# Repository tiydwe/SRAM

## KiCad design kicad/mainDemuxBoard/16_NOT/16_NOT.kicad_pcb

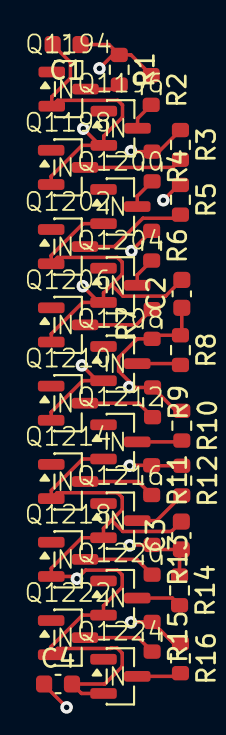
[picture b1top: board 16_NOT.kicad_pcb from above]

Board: 4 copper layers, 36 parts (0 on the bottom side), 18 nets.

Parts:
C1, C2, C3, C4: 100nC; C_0603_1608Metric
Q1194, Q1196, Q1198, Q1200, Q1202, Q1204, Q1206, Q1208, Q1210, Q1212, Q1214, Q1216, Q1218, Q1220, Q1222, Q1224: Q_NMOS_GSD; SOT-23-N
R1, R2, R3, R4, R5, R6, R7, R8, R9, R10, R11, R12, R13, R14, R15, R16: 10kR; R_0603_1608Metric

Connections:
+5V: C1.1, C2.1, C3.1, C4.1, R1.1, R2.1, R3.1, R4.1, R5.1, R6.1, R7.1, R8.1, R9.1, R10.1, R11.1, R12.1, R13.1, R14.1, R15.1, R16.1
/~Y_{0}: Q1194.3 (D), R1.2
/~Y_{1}: Q1196.3 (D), R2.2
/~Y_{2}: Q1198.3 (D), R3.2
/~Y_{3}: Q1200.3 (D), R4.2
/~Y_{4}: Q1202.3 (D), R5.2
/~Y_{5}: Q1204.3 (D), R6.2
/~Y_{6}: Q1206.3 (D), R7.2
/~Y_{7}: Q1208.3 (D), R8.2
/~Y_{8}: Q1210.3 (D), R9.2
/~Y_{9}: Q1212.3 (D), R10.2
/~Y_{10}: Q1214.3 (D), R11.2
/~Y_{11}: Q1216.3 (D), R12.2
/~Y_{12}: Q1218.3 (D), R13.2
/~Y_{13}: Q1220.3 (D), R14.2
/~Y_{14}: Q1222.3 (D), R15.2
/~Y_{15}: Q1224.3 (D), R16.2
GND: C1.2, C2.2, C3.2, C4.2, Q1194.2 (S), Q1196.2 (S), Q1198.2 (S), Q1200.2 (S), Q1202.2 (S), Q1204.2 (S), Q1206.2 (S), Q1208.2 (S), Q1210.2 (S), Q1212.2 (S), Q1214.2 (S), Q1216.2 (S), Q1218.2 (S), Q1220.2 (S), Q1222.2 (S), Q1224.2 (S)

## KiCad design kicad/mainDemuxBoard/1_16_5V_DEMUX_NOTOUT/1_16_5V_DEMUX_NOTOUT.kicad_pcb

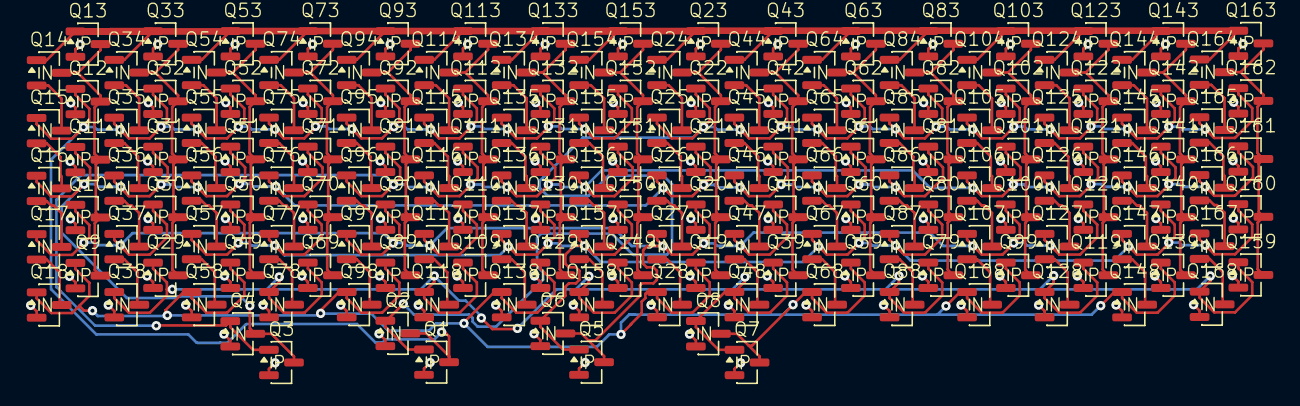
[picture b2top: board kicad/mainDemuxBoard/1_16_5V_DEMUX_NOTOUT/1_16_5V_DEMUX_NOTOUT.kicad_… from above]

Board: 4 copper layers, 168 parts (0 on the bottom side), 91 nets.

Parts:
Q1, Q3, Q5, Q7, Q9, Q10, Q11, Q12, Q13, Q19, Q20, Q21, Q22, Q23, Q29, Q30, Q31, Q32, Q33, Q39, Q40, Q41, Q42, Q43, Q49, Q50, Q51, Q52, Q53, Q59, Q60, Q61, Q62, Q63, Q69, Q70, Q71, Q72, Q73, Q79, Q80, Q81, Q82, Q83, Q89, Q90, Q91, Q92, Q93, Q99, Q100, Q101, Q102, Q103, Q109, Q110, Q111, Q112, Q113, Q119, Q120, Q121, Q122, Q123, Q129, Q130, Q131, Q132, Q133, Q139, Q140, Q141, Q142, Q143, Q149, Q150, Q151, Q152, Q153, Q159, Q160, Q161, Q162, Q163: Q_PMOS_GSD; SOT-23-P
Q2, Q4, Q6, Q8, Q14, Q15, Q16, Q17, Q18, Q24, Q25, Q26, Q27, Q28, Q34, Q35, Q36, Q37, Q38, Q44, Q45, Q46, Q47, Q48, Q54, Q55, Q56, Q57, Q58, Q64, Q65, Q66, Q67, Q68, Q74, Q75, Q76, Q77, Q78, Q84, Q85, Q86, Q87, Q88, Q94, Q95, Q96, Q97, Q98, Q104, Q105, Q106, Q107, Q108, Q114, Q115, Q116, Q117, Q118, Q124, Q125, Q126, Q127, Q128, Q134, Q135, Q136, Q137, Q138, Q144, Q145, Q146, Q147, Q148, Q154, Q155, Q156, Q157, Q158, Q164, Q165, Q166, Q167, Q168: Q_NMOS_GSD; SOT-23-N

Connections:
+5V: Q1.2 (S), Q3.2 (S), Q5.2 (S), Q7.2 (S), Q9.2 (S), Q10.2 (S), Q11.2 (S), Q12.2 (S), Q13.2 (S), Q19.2 (S), Q20.2 (S), Q21.2 (S), Q22.2 (S), Q23.2 (S), Q29.2 (S), Q30.2 (S), Q31.2 (S), Q32.2 (S), Q33.2 (S), Q39.2 (S), Q40.2 (S), Q41.2 (S), Q42.2 (S), Q43.2 (S), Q49.2 (S), Q50.2 (S), Q51.2 (S), Q52.2 (S), Q53.2 (S), Q59.2 (S), Q60.2 (S), Q61.2 (S), Q62.2 (S), Q63.2 (S), Q69.2 (S), Q70.2 (S), Q71.2 (S), Q72.2 (S), Q73.2 (S), Q79.2 (S), Q80.2 (S), Q81.2 (S), Q82.2 (S), Q83.2 (S), Q89.2 (S), Q90.2 (S), Q91.2 (S), Q92.2 (S), Q93.2 (S), Q99.2 (S), Q100.2 (S), Q101.2 (S), Q102.2 (S), Q103.2 (S), Q109.2 (S), Q110.2 (S), Q111.2 (S), Q112.2 (S), Q113.2 (S), Q119.2 (S), Q120.2 (S), Q121.2 (S), Q122.2 (S), Q123.2 (S), Q129.2 (S), Q130.2 (S), Q131.2 (S), Q132.2 (S), Q133.2 (S), Q139.2 (S), Q140.2 (S), Q141.2 (S), Q142.2 (S), Q143.2 (S), Q149.2 (S), Q150.2 (S), Q151.2 (S), Q152.2 (S), Q153.2 (S), Q159.2 (S), Q160.2 (S), Q161.2 (S), Q162.2 (S), Q163.2 (S)
/5VNOT1/Y: Q3.3 (D), Q4.3 (D), Q11.1 (G), Q16.1 (G), Q21.1 (G), Q26.1 (G), Q31.1 (G), Q36.1 (G), Q41.1 (G), Q46.1 (G), Q51.1 (G), Q56.1 (G), Q61.1 (G), Q66.1 (G), Q71.1 (G), Q76.1 (G), Q81.1 (G), Q86.1 (G)
/5VNOT2/Y: Q5.3 (D), Q6.3 (D), Q10.1 (G), Q17.1 (G), Q20.1 (G), Q27.1 (G), Q30.1 (G), Q37.1 (G), Q40.1 (G), Q47.1 (G), Q90.1 (G), Q97.1 (G), Q100.1 (G), Q107.1 (G), Q110.1 (G), Q117.1 (G), Q120.1 (G), Q127.1 (G)
/5VNOT3/Y: Q7.3 (D), Q8.3 (D), Q9.1 (G), Q18.1 (G), Q19.1 (G), Q28.1 (G), Q49.1 (G), Q58.1 (G), Q59.1 (G), Q68.1 (G), Q89.1 (G), Q98.1 (G), Q99.1 (G), Q108.1 (G), Q129.1 (G), Q138.1 (G), Q139.1 (G), Q148.1 (G)
/5VNOT/Y: Q1.3 (D), Q2.3 (D), Q12.1 (G), Q15.1 (G), Q32.1 (G), Q35.1 (G), Q52.1 (G), Q55.1 (G), Q72.1 (G), Q75.1 (G), Q92.1 (G), Q95.1 (G), Q112.1 (G), Q115.1 (G), Q132.1 (G), Q135.1 (G), Q152.1 (G), Q155.1 (G)
/D: Q13.1 (G), Q14.1 (G), Q23.1 (G), Q24.1 (G), Q33.1 (G), Q34.1 (G), Q43.1 (G), Q44.1 (G), Q53.1 (G), Q54.1 (G), Q63.1 (G), Q64.1 (G), Q73.1 (G), Q74.1 (G), Q83.1 (G), Q84.1 (G), Q93.1 (G), Q94.1 (G), Q103.1 (G), Q104.1 (G), Q113.1 (G), Q114.1 (G), Q123.1 (G), Q124.1 (G), Q133.1 (G), Q134.1 (G), Q143.1 (G), Q144.1 (G), Q153.1 (G), Q154.1 (G), Q163.1 (G), Q164.1 (G)
/S_{0}: Q1.1 (G), Q2.1 (G), Q22.1 (G), Q25.1 (G), Q42.1 (G), Q45.1 (G), Q62.1 (G), Q65.1 (G), Q82.1 (G), Q85.1 (G), Q102.1 (G), Q105.1 (G), Q122.1 (G), Q125.1 (G), Q142.1 (G), Q145.1 (G), Q162.1 (G), Q165.1 (G)
/S_{1}: Q3.1 (G), Q4.1 (G), Q91.1 (G), Q96.1 (G), Q101.1 (G), Q106.1 (G), Q111.1 (G), Q116.1 (G), Q121.1 (G), Q126.1 (G), Q131.1 (G), Q136.1 (G), Q141.1 (G), Q146.1 (G), Q151.1 (G), Q156.1 (G), Q161.1 (G), Q166.1 (G)
/S_{2}: Q5.1 (G), Q6.1 (G), Q50.1 (G), Q57.1 (G), Q60.1 (G), Q67.1 (G), Q70.1 (G), Q77.1 (G), Q80.1 (G), Q87.1 (G), Q130.1 (G), Q137.1 (G), Q140.1 (G), Q147.1 (G), Q150.1 (G), Q157.1 (G), Q160.1 (G), Q167.1 (G)
/S_{3}: Q7.1 (G), Q8.1 (G), Q29.1 (G), Q38.1 (G), Q39.1 (G), Q48.1 (G), Q69.1 (G), Q78.1 (G), Q79.1 (G), Q88.1 (G), Q109.1 (G), Q118.1 (G), Q119.1 (G), Q128.1 (G), Q149.1 (G), Q158.1 (G), Q159.1 (G), Q168.1 (G)
/~Y_{0}: Q9.3 (D), Q10.3 (D), Q11.3 (D), Q12.3 (D), Q13.3 (D), Q14.3 (D)
/~Y_{1}: Q29.3 (D), Q30.3 (D), Q31.3 (D), Q32.3 (D), Q33.3 (D), Q34.3 (D)
/~Y_{2}: Q49.3 (D), Q50.3 (D), Q51.3 (D), Q52.3 (D), Q53.3 (D), Q54.3 (D)
/~Y_{3}: Q69.3 (D), Q70.3 (D), Q71.3 (D), Q72.3 (D), Q73.3 (D), Q74.3 (D)
/~Y_{4}: Q89.3 (D), Q90.3 (D), Q91.3 (D), Q92.3 (D), Q93.3 (D), Q94.3 (D)
/~Y_{5}: Q109.3 (D), Q110.3 (D), Q111.3 (D), Q112.3 (D), Q113.3 (D), Q114.3 (D)
/~Y_{6}: Q129.3 (D), Q130.3 (D), Q131.3 (D), Q132.3 (D), Q133.3 (D), Q134.3 (D)
/~Y_{7}: Q149.3 (D), Q150.3 (D), Q151.3 (D), Q152.3 (D), Q153.3 (D), Q154.3 (D)
/~Y_{8}: Q19.3 (D), Q20.3 (D), Q21.3 (D), Q22.3 (D), Q23.3 (D), Q24.3 (D)
/~Y_{9}: Q39.3 (D), Q40.3 (D), Q41.3 (D), Q42.3 (D), Q43.3 (D), Q44.3 (D)
/~Y_{10}: Q59.3 (D), Q60.3 (D), Q61.3 (D), Q62.3 (D), Q63.3 (D), Q64.3 (D)
/~Y_{11}: Q79.3 (D), Q80.3 (D), Q81.3 (D), Q82.3 (D), Q83.3 (D), Q84.3 (D)
/~Y_{12}: Q99.3 (D), Q100.3 (D), Q101.3 (D), Q102.3 (D), Q103.3 (D), Q104.3 (D)
/~Y_{13}: Q119.3 (D), Q120.3 (D), Q121.3 (D), Q122.3 (D), Q123.3 (D), Q124.3 (D)
/~Y_{14}: Q139.3 (D), Q140.3 (D), Q141.3 (D), Q142.3 (D), Q143.3 (D), Q144.3 (D)
/~Y_{15}: Q159.3 (D), Q160.3 (D), Q161.3 (D), Q162.3 (D), Q163.3 (D), Q164.3 (D)
GND: Q2.2 (S), Q4.2 (S), Q6.2 (S), Q8.2 (S), Q18.2 (S), Q28.2 (S), Q38.2 (S), Q48.2 (S), Q58.2 (S), Q68.2 (S), Q78.2 (S), Q88.2 (S), Q98.2 (S), Q108.2 (S), Q118.2 (S), Q128.2 (S), Q138.2 (S), Q148.2 (S), Q158.2 (S), Q168.2 (S)
unnamed: Q14.2 (S), Q15.3 (D)
unnamed: Q15.2 (S), Q16.3 (D)
unnamed: Q16.2 (S), Q17.3 (D)
unnamed: Q17.2 (S), Q18.3 (D)
unnamed: Q24.2 (S), Q25.3 (D)
unnamed: Q25.2 (S), Q26.3 (D)
unnamed: Q26.2 (S), Q27.3 (D)
unnamed: Q27.2 (S), Q28.3 (D)
unnamed: Q34.2 (S), Q35.3 (D)
unnamed: Q35.2 (S), Q36.3 (D)
unnamed: Q36.2 (S), Q37.3 (D)
unnamed: Q37.2 (S), Q38.3 (D)
unnamed: Q44.2 (S), Q45.3 (D)
unnamed: Q45.2 (S), Q46.3 (D)
unnamed: Q46.2 (S), Q47.3 (D)
unnamed: Q47.2 (S), Q48.3 (D)
unnamed: Q54.2 (S), Q55.3 (D)
unnamed: Q55.2 (S), Q56.3 (D)
unnamed: Q56.2 (S), Q57.3 (D)
unnamed: Q57.2 (S), Q58.3 (D)
unnamed: Q64.2 (S), Q65.3 (D)
unnamed: Q65.2 (S), Q66.3 (D)
unnamed: Q66.2 (S), Q67.3 (D)
unnamed: Q67.2 (S), Q68.3 (D)
unnamed: Q74.2 (S), Q75.3 (D)
unnamed: Q75.2 (S), Q76.3 (D)
unnamed: Q76.2 (S), Q77.3 (D)
unnamed: Q77.2 (S), Q78.3 (D)
unnamed: Q84.2 (S), Q85.3 (D)
unnamed: Q85.2 (S), Q86.3 (D)
unnamed: Q86.2 (S), Q87.3 (D)
unnamed: Q87.2 (S), Q88.3 (D)
unnamed: Q94.2 (S), Q95.3 (D)
unnamed: Q95.2 (S), Q96.3 (D)
unnamed: Q96.2 (S), Q97.3 (D)
unnamed: Q97.2 (S), Q98.3 (D)
unnamed: Q104.2 (S), Q105.3 (D)
unnamed: Q105.2 (S), Q106.3 (D)
unnamed: Q106.2 (S), Q107.3 (D)
unnamed: Q107.2 (S), Q108.3 (D)
unnamed: Q114.2 (S), Q115.3 (D)
unnamed: Q115.2 (S), Q116.3 (D)
unnamed: Q116.2 (S), Q117.3 (D)
unnamed: Q117.2 (S), Q118.3 (D)
unnamed: Q124.2 (S), Q125.3 (D)
unnamed: Q125.2 (S), Q126.3 (D)
unnamed: Q126.2 (S), Q127.3 (D)
unnamed: Q127.2 (S), Q128.3 (D)
unnamed: Q134.2 (S), Q135.3 (D)
unnamed: Q135.2 (S), Q136.3 (D)
unnamed: Q136.2 (S), Q137.3 (D)
unnamed: Q137.2 (S), Q138.3 (D)
unnamed: Q144.2 (S), Q145.3 (D)
unnamed: Q145.2 (S), Q146.3 (D)
unnamed: Q146.2 (S), Q147.3 (D)
unnamed: Q147.2 (S), Q148.3 (D)
unnamed: Q154.2 (S), Q155.3 (D)
unnamed: Q155.2 (S), Q156.3 (D)
unnamed: Q156.2 (S), Q157.3 (D)
unnamed: Q157.2 (S), Q158.3 (D)
unnamed: Q164.2 (S), Q165.3 (D)
unnamed: Q165.2 (S), Q166.3 (D)
unnamed: Q166.2 (S), Q167.3 (D)
unnamed: Q167.2 (S), Q168.3 (D)

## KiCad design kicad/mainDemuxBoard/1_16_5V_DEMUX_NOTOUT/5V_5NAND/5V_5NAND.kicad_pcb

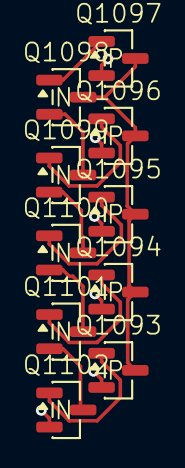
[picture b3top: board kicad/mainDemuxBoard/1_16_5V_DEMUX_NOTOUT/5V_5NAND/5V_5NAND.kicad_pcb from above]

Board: 4 copper layers, 10 parts (0 on the bottom side), 11 nets.

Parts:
Q1093, Q1094, Q1095, Q1096, Q1097: Q_PMOS_GSD; SOT-23-P
Q1098, Q1099, Q1100, Q1101, Q1102: Q_NMOS_GSD; SOT-23-N

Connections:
+5V: Q1093.2 (S), Q1094.2 (S), Q1095.2 (S), Q1096.2 (S), Q1097.2 (S)
/A_{0}: Q1097.1 (G), Q1098.1 (G)
/A_{1}: Q1096.1 (G), Q1099.1 (G)
/A_{2}: Q1095.1 (G), Q1100.1 (G)
/A_{3}: Q1094.1 (G), Q1101.1 (G)
/A_{4}: Q1093.1 (G), Q1102.1 (G)
/Y: Q1093.3 (D), Q1094.3 (D), Q1095.3 (D), Q1096.3 (D), Q1097.3 (D), Q1098.3 (D)
unnamed: Q1098.2 (S), Q1099.3 (D)
unnamed: Q1099.2 (S), Q1100.3 (D)
unnamed: Q1100.2 (S), Q1101.3 (D)
unnamed: Q1101.2 (S), Q1102.3 (D)

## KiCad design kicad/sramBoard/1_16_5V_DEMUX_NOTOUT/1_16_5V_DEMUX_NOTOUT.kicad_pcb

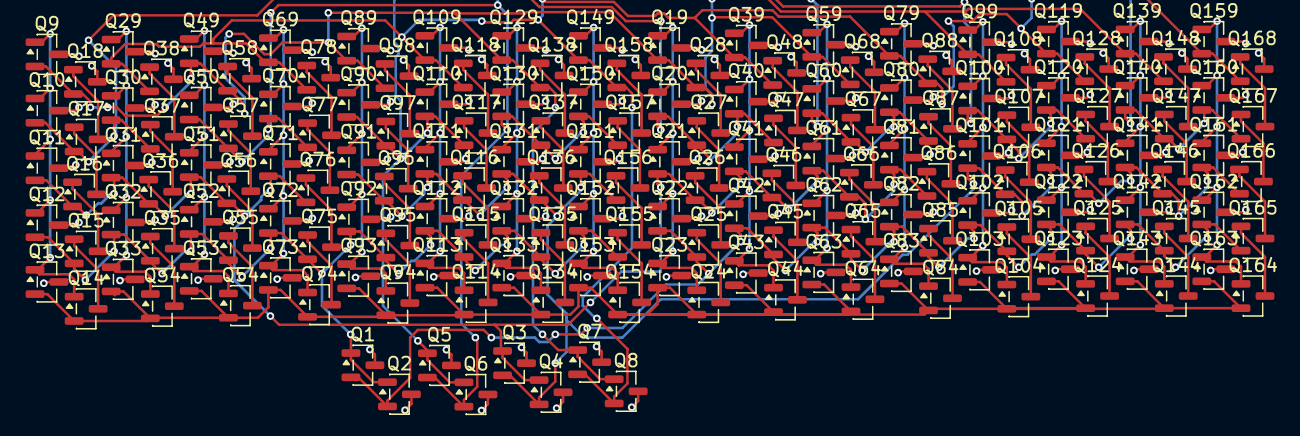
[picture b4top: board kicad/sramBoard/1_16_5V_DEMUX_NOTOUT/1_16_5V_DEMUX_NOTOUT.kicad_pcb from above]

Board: 4 copper layers, 168 parts (0 on the bottom side), 91 nets.

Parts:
Q1, Q3, Q5, Q7, Q9, Q10, Q11, Q12, Q13, Q19, Q20, Q21, Q22, Q23, Q29, Q30, Q31, Q32, Q33, Q39, Q40, Q41, Q42, Q43, Q49, Q50, Q51, Q52, Q53, Q59, Q60, Q61, Q62, Q63, Q69, Q70, Q71, Q72, Q73, Q79, Q80, Q81, Q82, Q83, Q89, Q90, Q91, Q92, Q93, Q99, Q100, Q101, Q102, Q103, Q109, Q110, Q111, Q112, Q113, Q119, Q120, Q121, Q122, Q123, Q129, Q130, Q131, Q132, Q133, Q139, Q140, Q141, Q142, Q143, Q149, Q150, Q151, Q152, Q153, Q159, Q160, Q161, Q162, Q163: PMOS; SOT-23
Q2, Q4, Q6, Q8, Q14, Q15, Q16, Q17, Q18, Q24, Q25, Q26, Q27, Q28, Q34, Q35, Q36, Q37, Q38, Q44, Q45, Q46, Q47, Q48, Q54, Q55, Q56, Q57, Q58, Q64, Q65, Q66, Q67, Q68, Q74, Q75, Q76, Q77, Q78, Q84, Q85, Q86, Q87, Q88, Q94, Q95, Q96, Q97, Q98, Q104, Q105, Q106, Q107, Q108, Q114, Q115, Q116, Q117, Q118, Q124, Q125, Q126, Q127, Q128, Q134, Q135, Q136, Q137, Q138, Q144, Q145, Q146, Q147, Q148, Q154, Q155, Q156, Q157, Q158, Q164, Q165, Q166, Q167, Q168: NMOS; SOT-23

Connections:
+5V: Q1.3 (S), Q3.3 (S), Q5.3 (S), Q7.3 (S), Q9.3 (S), Q10.3 (S), Q11.3 (S), Q12.3 (S), Q13.3 (S), Q19.3 (S), Q20.3 (S), Q21.3 (S), Q22.3 (S), Q23.3 (S), Q29.3 (S), Q30.3 (S), Q31.3 (S), Q32.3 (S), Q33.3 (S), Q39.3 (S), Q40.3 (S), Q41.3 (S), Q42.3 (S), Q43.3 (S), Q49.3 (S), Q50.3 (S), Q51.3 (S), Q52.3 (S), Q53.3 (S), Q59.3 (S), Q60.3 (S), Q61.3 (S), Q62.3 (S), Q63.3 (S), Q69.3 (S), Q70.3 (S), Q71.3 (S), Q72.3 (S), Q73.3 (S), Q79.3 (S), Q80.3 (S), Q81.3 (S), Q82.3 (S), Q83.3 (S), Q89.3 (S), Q90.3 (S), Q91.3 (S), Q92.3 (S), Q93.3 (S), Q99.3 (S), Q100.3 (S), Q101.3 (S), Q102.3 (S), Q103.3 (S), Q109.3 (S), Q110.3 (S), Q111.3 (S), Q112.3 (S), Q113.3 (S), Q119.3 (S), Q120.3 (S), Q121.3 (S), Q122.3 (S), Q123.3 (S), Q129.3 (S), Q130.3 (S), Q131.3 (S), Q132.3 (S), Q133.3 (S), Q139.3 (S), Q140.3 (S), Q141.3 (S), Q142.3 (S), Q143.3 (S), Q149.3 (S), Q150.3 (S), Q151.3 (S), Q152.3 (S), Q153.3 (S), Q159.3 (S), Q160.3 (S), Q161.3 (S), Q162.3 (S), Q163.3 (S)
/5VNOT1/Y: Q3.1 (D), Q4.1 (D), Q11.2 (G), Q16.2 (G), Q21.2 (G), Q26.2 (G), Q31.2 (G), Q36.2 (G), Q41.2 (G), Q46.2 (G), Q51.2 (G), Q56.2 (G), Q61.2 (G), Q66.2 (G), Q71.2 (G), Q76.2 (G), Q81.2 (G), Q86.2 (G)
/5VNOT2/Y: Q5.1 (D), Q6.1 (D), Q10.2 (G), Q17.2 (G), Q20.2 (G), Q27.2 (G), Q30.2 (G), Q37.2 (G), Q40.2 (G), Q47.2 (G), Q90.2 (G), Q97.2 (G), Q100.2 (G), Q107.2 (G), Q110.2 (G), Q117.2 (G), Q120.2 (G), Q127.2 (G)
/5VNOT3/Y: Q7.1 (D), Q8.1 (D), Q9.2 (G), Q18.2 (G), Q19.2 (G), Q28.2 (G), Q49.2 (G), Q58.2 (G), Q59.2 (G), Q68.2 (G), Q89.2 (G), Q98.2 (G), Q99.2 (G), Q108.2 (G), Q129.2 (G), Q138.2 (G), Q139.2 (G), Q148.2 (G)
/5VNOT/Y: Q1.1 (D), Q2.1 (D), Q12.2 (G), Q15.2 (G), Q32.2 (G), Q35.2 (G), Q52.2 (G), Q55.2 (G), Q72.2 (G), Q75.2 (G), Q92.2 (G), Q95.2 (G), Q112.2 (G), Q115.2 (G), Q132.2 (G), Q135.2 (G), Q152.2 (G), Q155.2 (G)
/D: Q13.2 (G), Q14.2 (G), Q23.2 (G), Q24.2 (G), Q33.2 (G), Q34.2 (G), Q43.2 (G), Q44.2 (G), Q53.2 (G), Q54.2 (G), Q63.2 (G), Q64.2 (G), Q73.2 (G), Q74.2 (G), Q83.2 (G), Q84.2 (G), Q93.2 (G), Q94.2 (G), Q103.2 (G), Q104.2 (G), Q113.2 (G), Q114.2 (G), Q123.2 (G), Q124.2 (G), Q133.2 (G), Q134.2 (G), Q143.2 (G), Q144.2 (G), Q153.2 (G), Q154.2 (G), Q163.2 (G), Q164.2 (G)
/S_{0}: Q1.2 (G), Q2.2 (G), Q22.2 (G), Q25.2 (G), Q42.2 (G), Q45.2 (G), Q62.2 (G), Q65.2 (G), Q82.2 (G), Q85.2 (G), Q102.2 (G), Q105.2 (G), Q122.2 (G), Q125.2 (G), Q142.2 (G), Q145.2 (G), Q162.2 (G), Q165.2 (G)
/S_{1}: Q3.2 (G), Q4.2 (G), Q91.2 (G), Q96.2 (G), Q101.2 (G), Q106.2 (G), Q111.2 (G), Q116.2 (G), Q121.2 (G), Q126.2 (G), Q131.2 (G), Q136.2 (G), Q141.2 (G), Q146.2 (G), Q151.2 (G), Q156.2 (G), Q161.2 (G), Q166.2 (G)
/S_{2}: Q5.2 (G), Q6.2 (G), Q50.2 (G), Q57.2 (G), Q60.2 (G), Q67.2 (G), Q70.2 (G), Q77.2 (G), Q80.2 (G), Q87.2 (G), Q130.2 (G), Q137.2 (G), Q140.2 (G), Q147.2 (G), Q150.2 (G), Q157.2 (G), Q160.2 (G), Q167.2 (G)
/S_{3}: Q7.2 (G), Q8.2 (G), Q29.2 (G), Q38.2 (G), Q39.2 (G), Q48.2 (G), Q69.2 (G), Q78.2 (G), Q79.2 (G), Q88.2 (G), Q109.2 (G), Q118.2 (G), Q119.2 (G), Q128.2 (G), Q149.2 (G), Q158.2 (G), Q159.2 (G), Q168.2 (G)
/~Y_{0}: Q9.1 (D), Q10.1 (D), Q11.1 (D), Q12.1 (D), Q13.1 (D), Q14.1 (D)
/~Y_{1}: Q29.1 (D), Q30.1 (D), Q31.1 (D), Q32.1 (D), Q33.1 (D), Q34.1 (D)
/~Y_{2}: Q49.1 (D), Q50.1 (D), Q51.1 (D), Q52.1 (D), Q53.1 (D), Q54.1 (D)
/~Y_{3}: Q69.1 (D), Q70.1 (D), Q71.1 (D), Q72.1 (D), Q73.1 (D), Q74.1 (D)
/~Y_{4}: Q89.1 (D), Q90.1 (D), Q91.1 (D), Q92.1 (D), Q93.1 (D), Q94.1 (D)
/~Y_{5}: Q109.1 (D), Q110.1 (D), Q111.1 (D), Q112.1 (D), Q113.1 (D), Q114.1 (D)
/~Y_{6}: Q129.1 (D), Q130.1 (D), Q131.1 (D), Q132.1 (D), Q133.1 (D), Q134.1 (D)
/~Y_{7}: Q149.1 (D), Q150.1 (D), Q151.1 (D), Q152.1 (D), Q153.1 (D), Q154.1 (D)
/~Y_{8}: Q19.1 (D), Q20.1 (D), Q21.1 (D), Q22.1 (D), Q23.1 (D), Q24.1 (D)
/~Y_{9}: Q39.1 (D), Q40.1 (D), Q41.1 (D), Q42.1 (D), Q43.1 (D), Q44.1 (D)
/~Y_{10}: Q59.1 (D), Q60.1 (D), Q61.1 (D), Q62.1 (D), Q63.1 (D), Q64.1 (D)
/~Y_{11}: Q79.1 (D), Q80.1 (D), Q81.1 (D), Q82.1 (D), Q83.1 (D), Q84.1 (D)
/~Y_{12}: Q99.1 (D), Q100.1 (D), Q101.1 (D), Q102.1 (D), Q103.1 (D), Q104.1 (D)
/~Y_{13}: Q119.1 (D), Q120.1 (D), Q121.1 (D), Q122.1 (D), Q123.1 (D), Q124.1 (D)
/~Y_{14}: Q139.1 (D), Q140.1 (D), Q141.1 (D), Q142.1 (D), Q143.1 (D), Q144.1 (D)
/~Y_{15}: Q159.1 (D), Q160.1 (D), Q161.1 (D), Q162.1 (D), Q163.1 (D), Q164.1 (D)
GND: Q2.3 (S), Q4.3 (S), Q6.3 (S), Q8.3 (S), Q18.3 (S), Q28.3 (S), Q38.3 (S), Q48.3 (S), Q58.3 (S), Q68.3 (S), Q78.3 (S), Q88.3 (S), Q98.3 (S), Q108.3 (S), Q118.3 (S), Q128.3 (S), Q138.3 (S), Q148.3 (S), Q158.3 (S), Q168.3 (S)
unnamed: Q14.3 (S), Q15.1 (D)
unnamed: Q15.3 (S), Q16.1 (D)
unnamed: Q16.3 (S), Q17.1 (D)
unnamed: Q17.3 (S), Q18.1 (D)
unnamed: Q24.3 (S), Q25.1 (D)
unnamed: Q25.3 (S), Q26.1 (D)
unnamed: Q26.3 (S), Q27.1 (D)
unnamed: Q27.3 (S), Q28.1 (D)
unnamed: Q34.3 (S), Q35.1 (D)
unnamed: Q35.3 (S), Q36.1 (D)
unnamed: Q36.3 (S), Q37.1 (D)
unnamed: Q37.3 (S), Q38.1 (D)
unnamed: Q44.3 (S), Q45.1 (D)
unnamed: Q45.3 (S), Q46.1 (D)
unnamed: Q46.3 (S), Q47.1 (D)
unnamed: Q47.3 (S), Q48.1 (D)
unnamed: Q54.3 (S), Q55.1 (D)
unnamed: Q55.3 (S), Q56.1 (D)
unnamed: Q56.3 (S), Q57.1 (D)
unnamed: Q57.3 (S), Q58.1 (D)
unnamed: Q64.3 (S), Q65.1 (D)
unnamed: Q65.3 (S), Q66.1 (D)
unnamed: Q66.3 (S), Q67.1 (D)
unnamed: Q67.3 (S), Q68.1 (D)
unnamed: Q74.3 (S), Q75.1 (D)
unnamed: Q75.3 (S), Q76.1 (D)
unnamed: Q76.3 (S), Q77.1 (D)
unnamed: Q77.3 (S), Q78.1 (D)
unnamed: Q84.3 (S), Q85.1 (D)
unnamed: Q85.3 (S), Q86.1 (D)
unnamed: Q86.3 (S), Q87.1 (D)
unnamed: Q87.3 (S), Q88.1 (D)
unnamed: Q94.3 (S), Q95.1 (D)
unnamed: Q95.3 (S), Q96.1 (D)
unnamed: Q96.3 (S), Q97.1 (D)
unnamed: Q97.3 (S), Q98.1 (D)
unnamed: Q104.3 (S), Q105.1 (D)
unnamed: Q105.3 (S), Q106.1 (D)
unnamed: Q106.3 (S), Q107.1 (D)
unnamed: Q107.3 (S), Q108.1 (D)
unnamed: Q114.3 (S), Q115.1 (D)
unnamed: Q115.3 (S), Q116.1 (D)
unnamed: Q116.3 (S), Q117.1 (D)
unnamed: Q117.3 (S), Q118.1 (D)
unnamed: Q124.3 (S), Q125.1 (D)
unnamed: Q125.3 (S), Q126.1 (D)
unnamed: Q126.3 (S), Q127.1 (D)
unnamed: Q127.3 (S), Q128.1 (D)
unnamed: Q134.3 (S), Q135.1 (D)
unnamed: Q135.3 (S), Q136.1 (D)
unnamed: Q136.3 (S), Q137.1 (D)
unnamed: Q137.3 (S), Q138.1 (D)
unnamed: Q144.3 (S), Q145.1 (D)
unnamed: Q145.3 (S), Q146.1 (D)
unnamed: Q146.3 (S), Q147.1 (D)
unnamed: Q147.3 (S), Q148.1 (D)
unnamed: Q154.3 (S), Q155.1 (D)
unnamed: Q155.3 (S), Q156.1 (D)
unnamed: Q156.3 (S), Q157.1 (D)
unnamed: Q157.3 (S), Q158.1 (D)
unnamed: Q164.3 (S), Q165.1 (D)
unnamed: Q165.3 (S), Q166.1 (D)
unnamed: Q166.3 (S), Q167.1 (D)
unnamed: Q167.3 (S), Q168.1 (D)

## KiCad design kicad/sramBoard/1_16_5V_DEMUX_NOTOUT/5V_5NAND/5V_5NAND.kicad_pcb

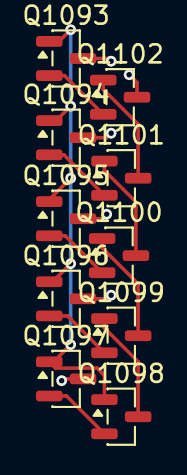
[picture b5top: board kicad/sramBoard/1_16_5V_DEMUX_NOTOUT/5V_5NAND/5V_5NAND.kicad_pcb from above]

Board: 4 copper layers, 10 parts (0 on the bottom side), 11 nets.

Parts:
Q1093, Q1094, Q1095, Q1096, Q1097: PMOS; SOT-23
Q1098, Q1099, Q1100, Q1101, Q1102: NMOS; SOT-23

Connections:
+5V: Q1093.3 (S), Q1094.3 (S), Q1095.3 (S), Q1096.3 (S), Q1097.3 (S)
/A_{0}: Q1097.2 (G), Q1098.2 (G)
/A_{1}: Q1096.2 (G), Q1099.2 (G)
/A_{2}: Q1095.2 (G), Q1100.2 (G)
/A_{3}: Q1094.2 (G), Q1101.2 (G)
/A_{4}: Q1093.2 (G), Q1102.2 (G)
/Y: Q1093.1 (D), Q1094.1 (D), Q1095.1 (D), Q1096.1 (D), Q1097.1 (D), Q1098.1 (D)
unnamed: Q1098.3 (S), Q1099.1 (D)
unnamed: Q1099.3 (S), Q1100.1 (D)
unnamed: Q1100.3 (S), Q1101.1 (D)
unnamed: Q1101.3 (S), Q1102.1 (D)
